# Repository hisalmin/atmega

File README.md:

atmega
======

Miscellaneous ATmega boards

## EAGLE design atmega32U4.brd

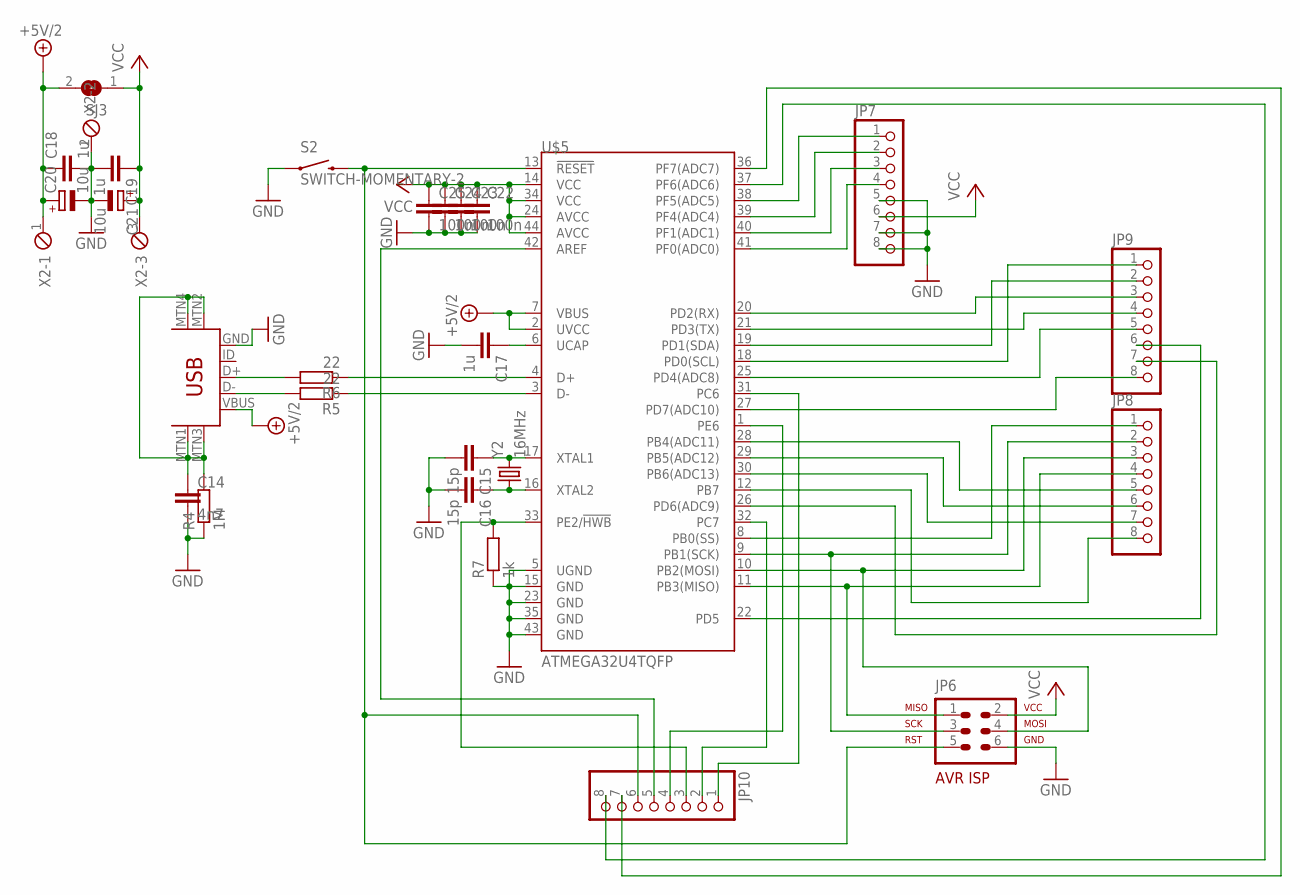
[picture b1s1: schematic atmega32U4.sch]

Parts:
C14: 4n7; C0603
C15, C16: 15p; C0603
C17: 1u; C0603
C18, C19: 1u; C0805
C20, C21: 10u; SMC_B
C22, C23, C24, C25: 100n; C0603
JP6: AVR-ISP-6VERT; AVR-ISP-6
JP7, JP8, JP9, JP10: PINHD_FIXEDPAD_ROUND-1X8; 1X08_ROUND
R4: 1M; R0603
R5, R6: 22; R0603
R7: 1k; R0603
S2: SWITCH-MOMENTARY-2; TACTILE_SWITCH_TALL
SJ3: SJ_SMALL; SJ_2S-NO
U$3: USB-MINIB-5PIN; USB-MINIB
U$5: ATMEGA32U4TQFP; TQFP44
X2: MPT3; 3POL254
Y2: 16MHz; CRYSTAL-SMD-5X3

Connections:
+5V/2: C18.1, C20.+, SJ3.2, U$3.VBUS, U$5.2 (UVCC), U$5.7 (VBUS), X2.1
AREF: JP10.5, U$5.42 (AREF)
B0: JP8.1, U$5.8 (PB0(SS))
B1: JP6.3, JP8.2, U$5.9 (PB1(SCK))
B2: JP6.4, JP8.3, U$5.10 (PB2(MOSI))
B3: JP6.1, JP8.4, U$5.11 (PB3(MISO))
B4: JP8.5, U$5.28 (PB4(ADC11))
B5: JP8.6, U$5.29 (PB5(ADC12))
B6: JP8.7, U$5.30 (PB6(ADC13))
B7: JP8.8, U$5.12 (PB7)
C6: JP10.1, U$5.31 (PC6)
C7: JP10.2, U$5.32 (PC7)
D0: JP9.1, U$5.18 (PD0(SCL))
D1: JP9.2, U$5.19 (PD1(SDA))
D2: JP9.3, U$5.20 (PD2(RX))
D3: JP9.4, U$5.21 (PD3(TX))
D4: JP9.5, U$5.25 (PD4(ADC8))
D5: JP9.6, U$5.22 (PD5)
D6: JP9.7, U$5.26 (PD6(ADC9))
D7: JP9.8, U$5.27 (PD7(ADC10))
E2: JP10.3, R7.2, U$5.33 (PE2/!HWB)
E6: JP10.4, U$5.1 (PE6)
F0: JP7.4, U$5.41 (PF0(ADC0))
F1: JP7.3, U$5.40 (PF1(ADC1))
F4: JP7.2, U$5.39 (PF4(ADC4))
F5: JP7.1, U$5.38 (PF5(ADC5))
F6: JP10.8, U$5.37 (PF6(ADC6))
F7: JP10.7, U$5.36 (PF7(ADC7))
GND: C14.2, C15.2, C16.2, C17.2, C18.2, C19.2, C20.-, C21.-, C22.2, C23.2, C24.2, C25.2, JP6.6, JP7.5, JP7.7, JP7.8, R4.1, R7.1, S2.A2 (1), U$3.GND, U$5.5 (UGND), U$5.15 (GND), U$5.23 (GND), U$5.35 (GND), U$5.43 (GND), X2.2
MTN1: C14.1, R4.2, U$3.MTN1 (MTN2), U$3.MTN2 (MTN3), U$3.MTN3 (MTN1), U$3.MTN4
unnamed: R6.2, U$3.D+
unnamed: R5.2, U$3.D-
unnamed: C15.1, U$5.17 (XTAL1), Y2.3 (2)
unnamed: C16.1, U$5.16 (XTAL2), Y2.1
unnamed: R6.1, U$5.4 (D+)
unnamed: R5.1, U$5.3 (D-)
unnamed: C17.1, U$5.6 (UCAP)
RST: JP6.5, JP10.6, S2.B2 (2), U$5.13 (!RESET)
VCC: C19.1, C21.+, C22.1, C23.1, C24.1, C25.1, JP6.2, JP7.6, SJ3.1, U$5.14 (VCC), U$5.24 (AVCC), U$5.34 (VCC), U$5.44 (AVCC), X2.3

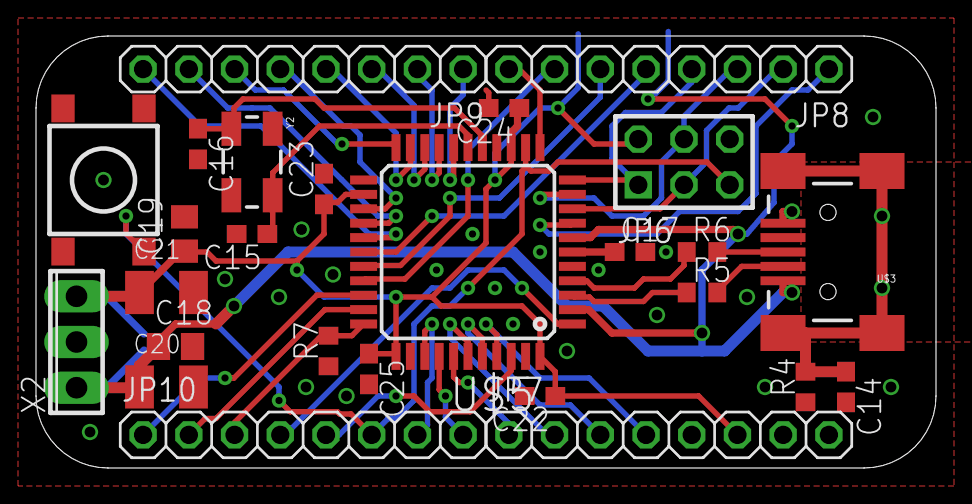
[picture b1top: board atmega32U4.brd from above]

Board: 2 copper layers, 50.0 x 24.0 mm, 27 parts (1 on the bottom side), 39 nets.

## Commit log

2013-03-06 A breakout board for Atmel Atmega32U4 (the same chip as on Arduino Leonardo, Teensy 2.0, etc.)

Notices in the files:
parts and their libraries:
SparkFun: Licensing: CC v3.0 Share-Alike You are welcome to use this library for commercial purposes.
